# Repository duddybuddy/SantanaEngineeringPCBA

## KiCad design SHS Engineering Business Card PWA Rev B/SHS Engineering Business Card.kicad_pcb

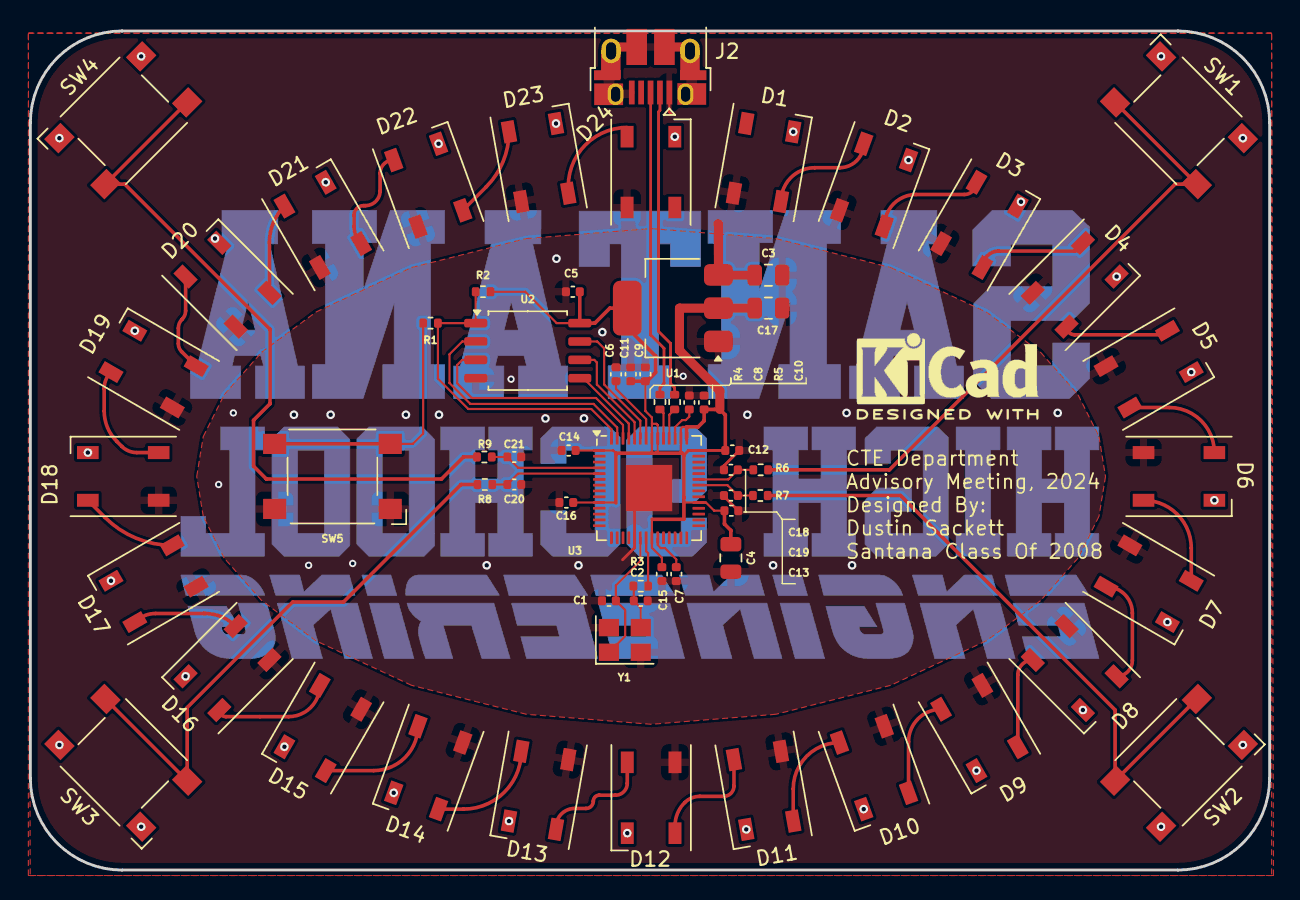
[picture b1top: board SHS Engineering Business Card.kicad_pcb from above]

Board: 2 copper layers, 85.7 x 58.0 mm, 66 parts (1 on the bottom side), 49 nets.

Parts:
C1, C2: 15p; C_0402_1005Metric
C3, C4, C17: 10u; C_0805_2012Metric
C5, C6, C7, C9, C11, C12, C13, C14, C15, C16, C18, C19, C20, C21: 100n; C_0402_1005Metric
C8, C10: 1u; C_0402_1005Metric
D1, D2, D3, D4, D5, D6, D7, D8, D9, D10, D11, D12, D13, D14, D15, D16, D17, D18, D19, D20, D21, D22, D23, D24: WS2812B; LED_WS2812B_PLCC4_5.0x5.0mm_P3.2mm
J2: USB_B_Micro; USB_Micro-B_Amphenol_10103594-0001LF_Horizontal
Logo1: Logo_Open_Hardware_Small; KiCad-Logo2_5mm_SilkScreen
Logo2: Logo_Open_Hardware_Small; Santana Engineering Logo
R1, R3, R6, R7, R8, R9: 1k; R_0402_1005Metric
R2: DNF; R_0402_1005Metric
R4, R5: 27; R_0402_1005Metric
SW1, SW2, SW3, SW4, SW5: SW_Push; SW_SPST_Omron_B3FS-100xP
U1: NCP1117-3.3_SOT223; SOT-223-3_TabPin2
U2: W25Q128JVS; SOIC-8_5.23x5.23mm_P1.27mm
U3: RP2040; QFN-56-1EP_7x7mm_P0.4mm_EP3.2x3.2mm
Y1: ABM8-272-T3; Crystal_SMD_3225-4Pin_3.2x2.5mm

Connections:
+1V1: C6.1, C7.1, C8.1, U3.23 (DVDD), U3.45 (VREG_VOUT), U3.50 (DVDD)
+3V3: C4.1, C5.1, C9.1, C10.1, C11.1, C12.1, C13.1, C14.1, C15.1, C16.1, C17.1, R2.1, U1.2 (VO), U2.8 (VCC), U3.1 (IOVDD), U3.10 (IOVDD), U3.22 (IOVDD), U3.33 (IOVDD), U3.42 (IOVDD), U3.43 (ADC_AVDD), U3.44 (VREG_IN), U3.48 (USB_VDD), U3.49 (IOVDD)
/GPIO2: C21.1, R9.1, U3.4 (GPIO2)
/GPIO3: C20.1, R8.1, U3.5 (GPIO3)
/GPIO24: C19.1, R7.1, U3.36 (GPIO24)
/GPIO25: C18.1, R6.1, U3.37 (GPIO25)
/QSPI_SCLK: U2.6 (CLK), U3.52 (QSPI_SCLK)
/QSPI_SD0: U2.5 (DI(IO0)), U3.53 (QSPI_SD0)
/QSPI_SD1: U2.2 (DO(IO1)), U3.55 (QSPI_SD1)
/QSPI_SD2: U2.3 (IO2), U3.54 (QSPI_SD2)
/QSPI_SD3: U2.7 (IO3), U3.51 (QSPI_SD3)
/QSPI_SS: R1.1, R2.2, U2.1 (~CS), U3.56 (QSPI_SS)
/USB_D+: J2.3 (D+), R4.1
/USB_D-: J2.2 (D-), R5.1
/XIN: C1.1, U3.20 (XIN), Y1.1
/XOUT: R3.1, U3.21 (XOUT)
/~USB_BOOT: R1.2, SW5.2
GND: C1.2, C2.2, C3.2, C4.2, C5.2, C6.2, C7.2, C8.2, C9.2, C10.2, C11.2, C12.2, C13.2, C14.2, C15.2, C16.2, C17.2, C18.2, C19.2, C20.2, C21.2, D1.3 (VSS), D2.3 (VSS), D3.3 (VSS), D4.3 (VSS), D5.3 (VSS), D6.3 (VSS), D7.3 (VSS), D8.3 (VSS), D9.3 (VSS), D10.3 (VSS), D11.3 (VSS), D12.3 (VSS), D13.3 (VSS), D14.3 (VSS), D15.3 (VSS), D16.3 (VSS), D17.3 (VSS), D18.3 (VSS), D19.3 (VSS), D20.3 (VSS), D21.3 (VSS), D22.3 (VSS), D23.3 (VSS), D24.3 (VSS), J2.5 (GND), J2.6 (Shield), SW1.1, SW2.1, SW3.1, SW4.1, SW5.1, U1.1 (GND), U2.4 (GND), U3.19 (TESTEN), U3.57 (GND), Y1.2, Y1.4
unnamed: C2.1, R3.2, Y1.3
unnamed: D1.2 (DOUT), D2.4 (DIN)
unnamed: D2.2 (DOUT), D3.4 (DIN)
unnamed: D3.2 (DOUT), D4.4 (DIN)
unnamed: D4.2 (DOUT), D5.4 (DIN)
unnamed: D5.2 (DOUT), D6.4 (DIN)
unnamed: D6.2 (DOUT), D7.4 (DIN)
unnamed: D7.2 (DOUT), D8.4 (DIN)
unnamed: D8.2 (DOUT), D9.4 (DIN)
unnamed: D9.2 (DOUT), D10.4 (DIN)
unnamed: D10.2 (DOUT), D11.4 (DIN)
unnamed: D11.2 (DOUT), D12.4 (DIN)
unnamed: D12.2 (DOUT), D13.4 (DIN)
unnamed: D13.2 (DOUT), D14.4 (DIN)
unnamed: D14.2 (DOUT), D15.4 (DIN)
unnamed: D15.2 (DOUT), D16.4 (DIN)
unnamed: D16.2 (DOUT), D17.4 (DIN)
unnamed: D17.2 (DOUT), D18.4 (DIN)
unnamed: D18.2 (DOUT), D19.4 (DIN)
unnamed: D19.2 (DOUT), D20.4 (DIN)
unnamed: D20.2 (DOUT), D21.4 (DIN)
unnamed: D21.2 (DOUT), D22.4 (DIN)
unnamed: D22.2 (DOUT), D23.4 (DIN)
unnamed: D23.2 (DOUT), D24.4 (DIN)
unnamed: R6.2, SW1.2
unnamed: R7.2, SW2.2
unnamed: R8.2, SW3.2
unnamed: R9.2, SW4.2
unnamed: R5.2, U3.46 (USB_DM)
unnamed: R4.2, U3.47 (USB_DP)
VBUS: C3.1, D1.1 (VDD), D2.1 (VDD), D3.1 (VDD), D4.1 (VDD), D5.1 (VDD), D6.1 (VDD), D7.1 (VDD), D8.1 (VDD), D9.1 (VDD), D10.1 (VDD), D11.1 (VDD), D12.1 (VDD), D13.1 (VDD), D14.1 (VDD), D15.1 (VDD), D16.1 (VDD), D17.1 (VDD), D18.1 (VDD), D19.1 (VDD), D20.1 (VDD), D21.1 (VDD), D22.1 (VDD), D23.1 (VDD), D24.1 (VDD), J2.1 (VBUS), U1.3 (VI)

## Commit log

2024-10-29 Add files via upload
    initial commit of PWA
